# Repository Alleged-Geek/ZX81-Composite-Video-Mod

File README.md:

# ZX81-Composite-Video-Mod
Here is my design of the ZX81 composite video mod

In this entry you will find 

Eagle PCB files should you want to modify the circuit in any way

A zipped file containing all the Gerber files which you can simply drag and drop on the JLPCB website (zxmod_2021-08-31.zip)

Images of the PCB layouts and schematic

An image of my populated V1 PCB (the one available for download here has the capacitors C3 and C5 in parallel on the bottom right hand side of the PCB)

Parts List

An excel spreadsheet in pdf format which contains a partslist of the components needed, as well as order codes and prices for Rapidonline.com

I couldn't get a reasonably priced 820pF Ceramic Disc capacitor from Rapid so I placed two capacitors in parallell (C3 and C5) and I suggest you solder a 
470pF and a 330pF in the space for them on the PCB. Alternaatively; if you do get an 820pF Capacitor just solder it into the C3 position.

As the minimum order for a PCB from JLPCB is 5, the order from Rapidonline.com has enough components to populate 5 circuit boards.

For more information, please visit my blog 

alleged-geek.blogspot.com

Alternatively, feel free to ask me any questions about the mod be sending me an email 

alleged_geek@aol.com

I hope that you find this useful

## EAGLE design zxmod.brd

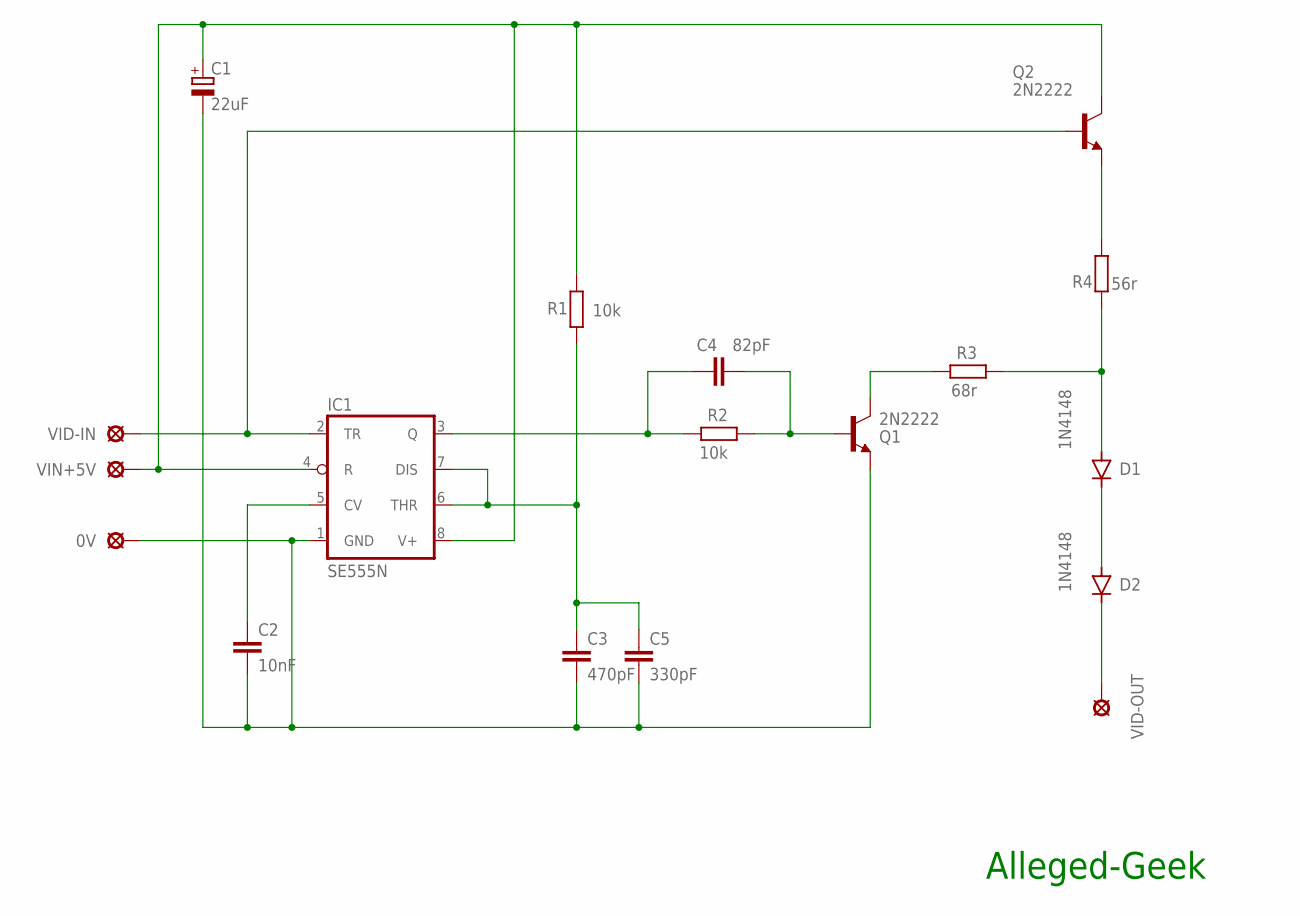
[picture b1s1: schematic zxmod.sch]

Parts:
0V: LSP10
C1: 22uF; E2,5-5
C2: 10nF; C050-030X075
C3: 470pF; C025-024X044
C4: 82pF; C025-025X050
C5: 330pF; C025-024X044
D1, D2: 1N4148; DO35-7
IC1: SE555N; DIL08
Q1, Q2: 2N2222; TO18
R1, R2: 10k; 0207/10
R3: 68r; 0207/10
R4: 56r; 0207/10
VID-IN: LSP10
VID-OUT: LSP10
VIN+5V: LSP10

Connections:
0V: 0V.MP, C1.-, C2.2, C3.2, C5.2, IC1.1 (GND), Q1.1 (E)
unnamed: C3.1, C5.1, IC1.6 (THR), IC1.7 (DIS), R1.1
unnamed: C4.1, IC1.3 (Q), R2.2
unnamed: C4.2, Q1.2 (B), R2.1
unnamed: Q1.3 (C), R3.2
unnamed: D1.A, R3.1, R4.1
unnamed: D1.C, D2.A
unnamed: Q2.1 (E), R4.2
unnamed: C2.1, IC1.5 (CV)
VID-IN: IC1.2 (TR), Q2.2 (B), VID-IN.MP
VID-OUT: D2.C, VID-OUT.MP
VIN-5V: C1.+, IC1.4 (R), IC1.8 (V+), Q2.3 (C), R1.2, VIN+5V.MP

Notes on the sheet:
Alleged-Geek

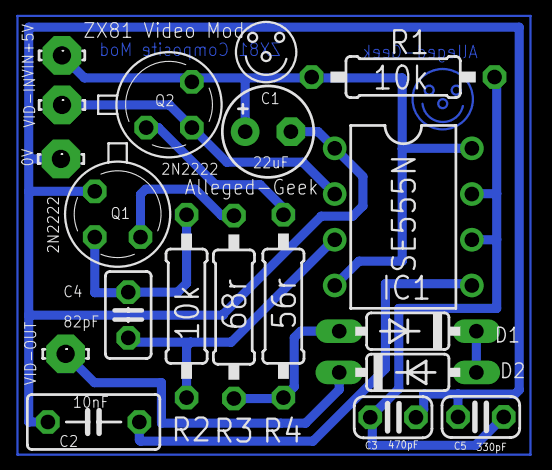
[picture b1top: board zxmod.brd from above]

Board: 2 copper layers, 18 parts (0 on the bottom side), 12 nets.
